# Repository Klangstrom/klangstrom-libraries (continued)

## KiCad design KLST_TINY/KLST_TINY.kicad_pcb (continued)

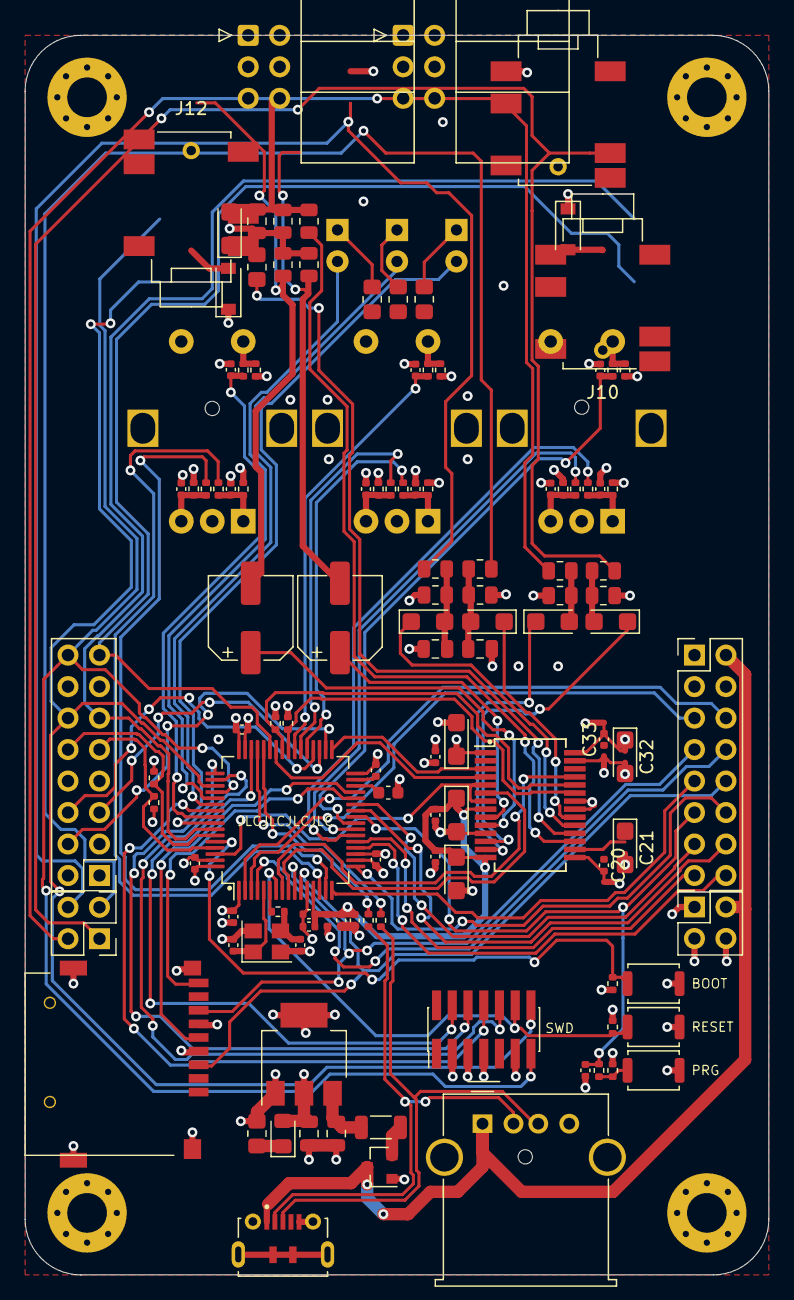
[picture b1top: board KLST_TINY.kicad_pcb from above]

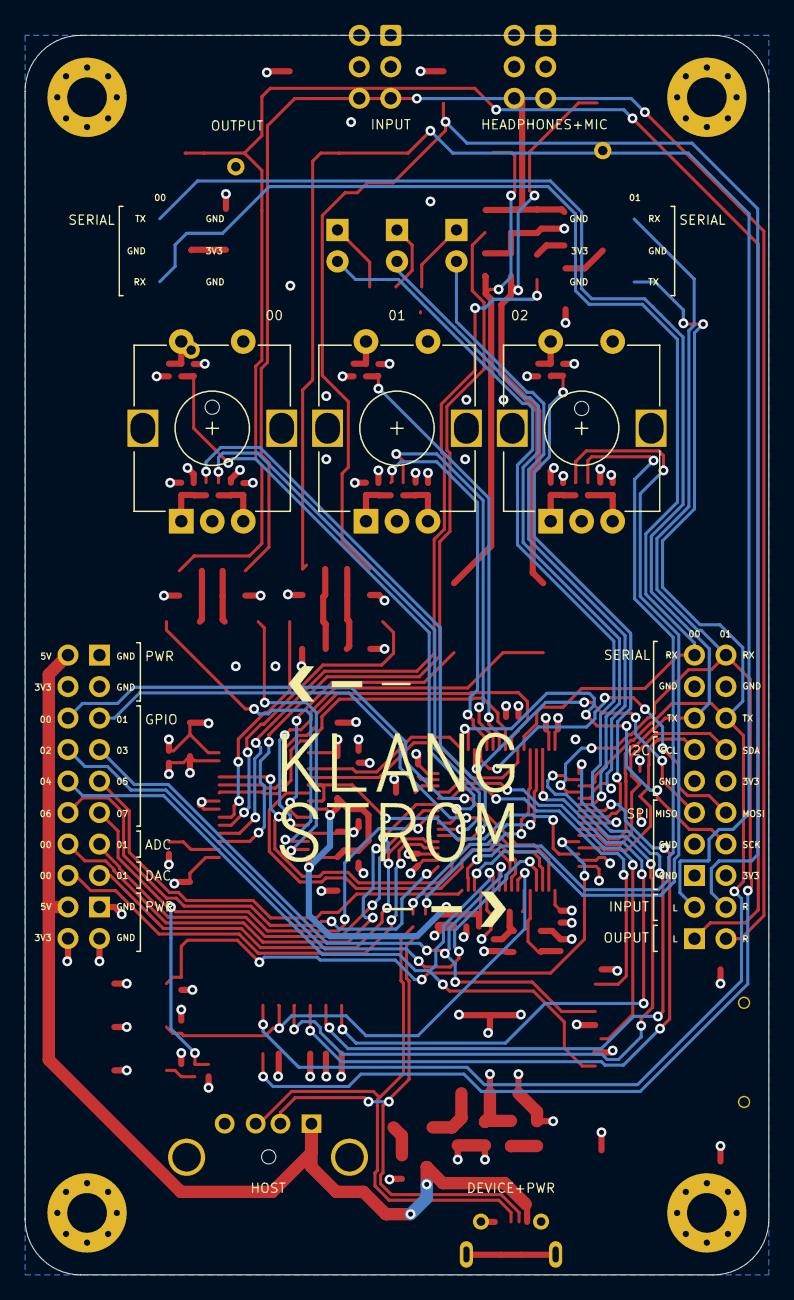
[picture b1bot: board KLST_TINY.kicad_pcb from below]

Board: 4 copper layers, 60.0 x 100.0 mm, 127 parts (7 on the bottom side), 99 nets.

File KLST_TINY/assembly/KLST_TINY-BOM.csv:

Comment,Designator,Footprint,LCSC
"12pF","C1,C2","Capacitor_SMD:C_0402_1005Metric","C1547"
"10nF","C10","Capacitor_SMD:C_0402_1005Metric","C15195"
"220uF","C16,C17","Capacitor_SMD:CP_Elec_6.3x5.4","C3345"
"10uF","C20,C29,C31,C33,C35","Capacitor_Tantalum_SMD:CP_EIA-3216-18_Kemet-A","C7171"
"1uF","C18,C22,C24,C26,C27","Capacitor_Tantalum_SMD:CP_EIA-3216-18_Kemet-A","C7175"
"220pF","C19,C23,C25","Capacitor_SMD:C_0805_2012Metric","C53172"
"10uF","C4,C5","Capacitor_SMD:C_0805_2012Metric","C15850"
"2.2uF","C6","Capacitor_SMD:C_0603_1608Metric","C23630"
"1uF","C7,C9,C11","Capacitor_SMD:C_0402_1005Metric","C52923"
"100nF","C3,C8,C12,C13,C14,C15,C21,C28,C30,C32,C34,C36,C37,C38,C39,C40,C41,C42,C43,C44","Capacitor_SMD:C_0402_1005Metric","C1525"
"LED","D1,D2,D3","LED_THT:LED_D3.0mm","DNF"
"LED","D4","LED_SMD:LED_0805_2012Metric_Pad1.15x1.40mm_HandSolder","C34499"
"D_Schottky","D5,D6","Diode_SMD:D_SOD-123","C8598"
"600Ω@100MHz","FB1","Inductor_SMD:L_1206_3216Metric","C73732"
"MountingHole","H1,H2,H3,H4","MountingHole:MountingHole_3.2mm_M3_Pad_Via","DNF"
"Micro_SD_Card_Card_Detect_SPI","J1","Connector_Card:microSD_SOFNG_TF-015","C113206"
"UART_00","J10","Connector_IDC:IDC-Header_2x03_P2.54mm_Horizontal","C146629"
"ADD-ON_PWR","J11","Connector_PinHeader_2.54mm:PinHeader_2x02_P2.54mm_Vertical","DNF"
"UART_01","J12","Connector_IDC:IDC-Header_2x03_P2.54mm_Horizontal","C146629"
"ADD-ON_AUDIO","J13","Connector_PinHeader_2.54mm:PinHeader_2x02_P2.54mm_Vertical","DNF"
"USB_A","J2","Connector_USB:USB_A_Molex_67643_Horizontal","C293351"
"USB_B_Micro","J3","KLST_TINY:SHOUHAN_MICROXNJ","C404969"
"GPIO+ANALOG_IO_PINS","J4","Connector_PinHeader_2.54mm:PinHeader_2x08_P2.54mm_Vertical","DNF"
"ARM_JTAG_SWD","J5","Connector_PinHeader_1.27mm:PinHeader_2x05_P1.27mm_Vertical_SMD","DNF"
"HEADPHONES+MIC","J6","KLST_TINY:Korean_Hroparts_Elec_PJ-316A-6A","C128987"
"LINE_IN","J7","KLST_TINY:Korean_Hroparts_Elec_PJ-316A-6A","C128987"
"LINE_OUT","J8","KLST_TINY:Korean_Hroparts_Elec_PJ-316A-6A","C128987"
"I2C_00+SPI_00","J9","Connector_PinHeader_2.54mm:PinHeader_2x08_P2.54mm_Vertical","DNF"
"39nH","L1","Inductor_SMD:L_0402_1005Metric","C26443"
"AO3401A","Q1","Package_TO_SOT_SMD:SOT-23","C693260"
"47K","R10,R11,R16,R22,R24","Resistor_SMD:R_0805_2012Metric","C17713"
"680R","R12","Resistor_SMD:R_0805_2012Metric","C17798"
"2.2K","R13,R14,R43,R44","Resistor_SMD:R_0402_1005Metric","C25879"
"330R","R15","Resistor_SMD:R_0805_2012Metric_Pad1.20x1.40mm_HandSolder","C17630"
"5.6K","R17,R18,R19,R20","Resistor_SMD:R_0805_2012Metric","C4382"
"22R","R1,R2","Resistor_SMD:R_0402_1005Metric","C25092"
"100R","R21,R23","Resistor_SMD:R_0805_2012Metric","C17408"
"1K","R26,R32,R38,R46","Resistor_SMD:R_0402_1005Metric","C11702"
"10R","R3","Resistor_SMD:R_0402_1005Metric","C25077"
"1K","R4,R5,R6,R7","Resistor_SMD:R_0805_2012Metric_Pad1.20x1.40mm_HandSolder","C17513"
"10K","R8,R9,R25,R27,R28,R29,R30,R31,R33,R34,R35,R36,R37,R39,R40,R41,R42,R45","Resistor_SMD:R_0402_1005Metric","C25744"
"BUTTON_BOOT_FLASH","SW1","Button_Switch_SMD:SW_Push_SPST_NO_Alps_SKRK","C115357"
"BUTTON_RESET","SW2","Button_Switch_SMD:SW_Push_SPST_NO_Alps_SKRK","C115357"
"ENCODER","SW3,SW4,SW5","Rotary_Encoder:RotaryEncoder_Alps_EC12E-Switch_Vertical_H20mm","DNF"
"BUTTON","SW6","Button_Switch_SMD:SW_Push_SPST_NO_Alps_SKRK","C115357"
"STM32F446RETx","U1","Package_QFP:LQFP-64_10x10mm_P0.5mm","C69336"
"AMS1117-3.3","U2","Package_TO_SOT_SMD:SOT-223-3_TabPin2","C6186"
"WM8731SEDS","U3","Package_SO:SSOP-28_5.3x10.2mm_P0.65mm","C323837"
"16MHz","Y1","Crystal:Crystal_SMD_3225-4Pin_3.2x2.5mm","C13738"

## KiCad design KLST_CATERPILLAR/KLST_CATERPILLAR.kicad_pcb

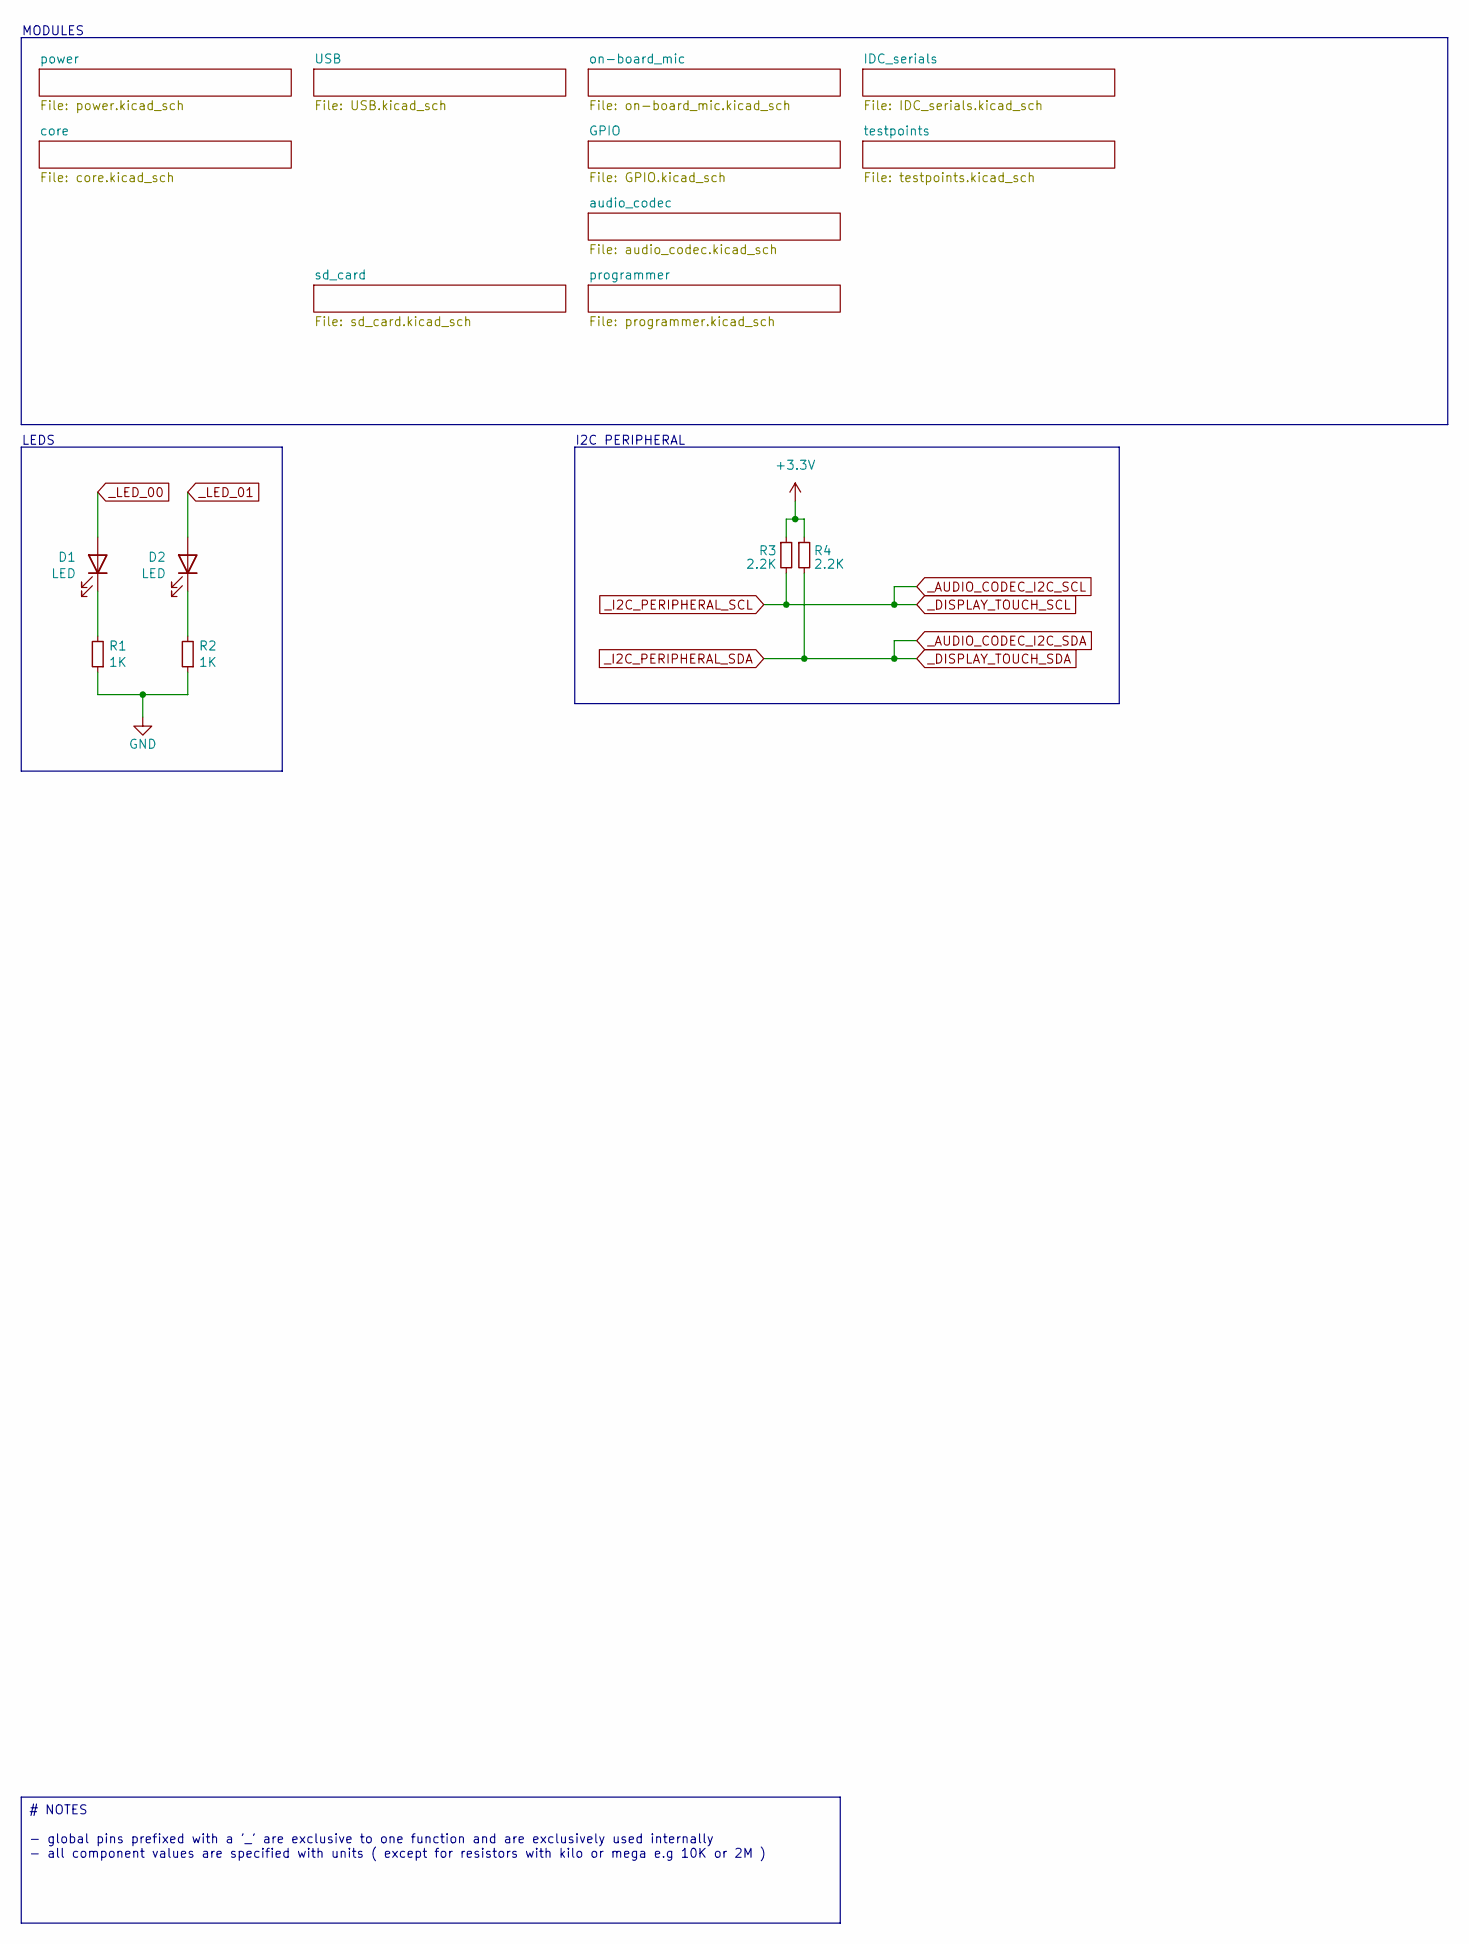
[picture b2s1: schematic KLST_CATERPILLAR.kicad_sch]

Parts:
D1, D2: LED; LED_0805_2012Metric; JLCPCB C34499
R1, R2: 1K; R_0805_2012Metric_Pad1.20x1.40mm_HandSolder; JLCPCB C17513
R3, R4: 2.2K; R_0402_1005Metric; JLCPCB C966835

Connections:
unnamed: D1.1 (K), R1.2
unnamed: D2.1 (K), R2.2
_AUDIO_CODEC_I2C_SCL: R3.2; also elsewhere on the board
_AUDIO_CODEC_I2C_SDA: R4.2; also elsewhere on the board
_LED_00: D1.2 (A); also elsewhere on the board
_LED_01: D2.2 (A); also elsewhere on the board

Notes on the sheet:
# NOTES - global pins prefixed with a '_' are exclusive to one function and are exclusively used internally - all component values are specified with units ( except for resistors with kilo or mega e.g 10K or 2M )
LEDS
I2C PERIPHERAL
MODULES

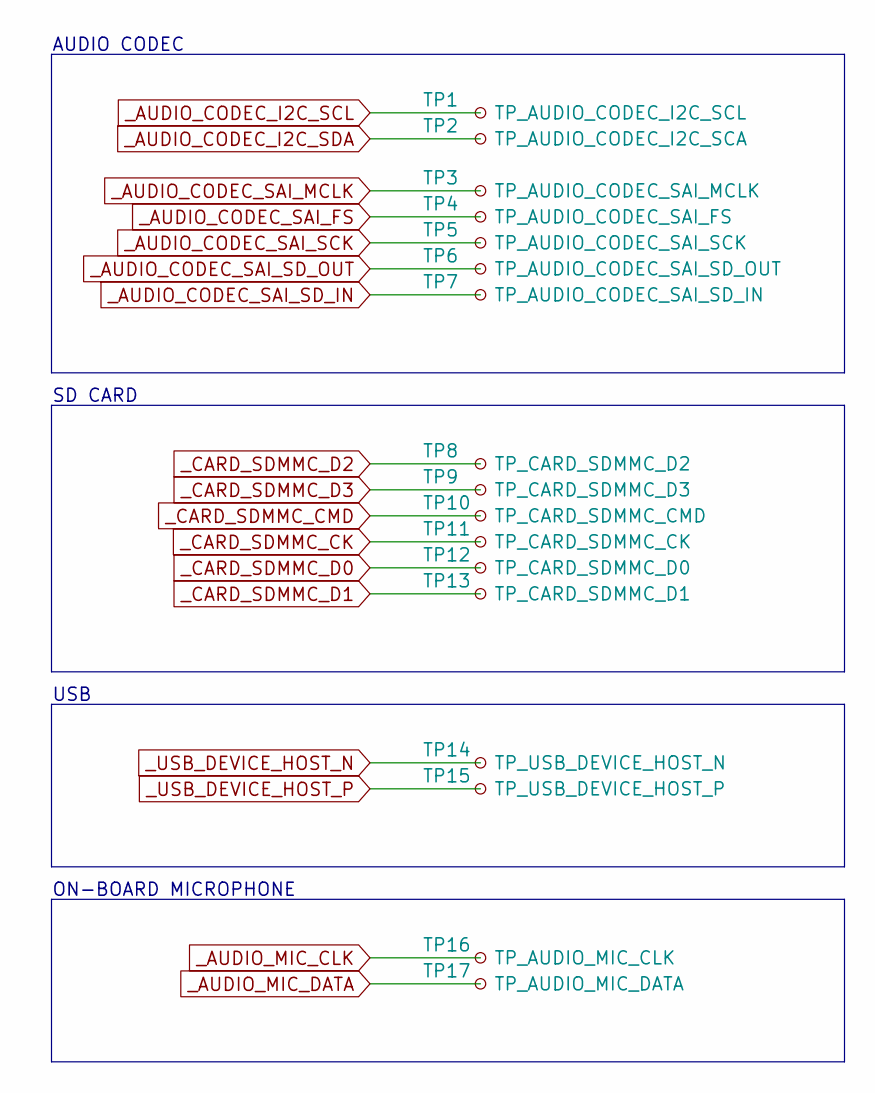
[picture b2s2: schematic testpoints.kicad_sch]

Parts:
TP1: TP_AUDIO_CODEC_I2C_SCL; TestPoint_Pad_D1.5mm
TP2: TP_AUDIO_CODEC_I2C_SCA; TestPoint_Pad_D1.5mm
TP3: TP_AUDIO_CODEC_SAI_MCLK; TestPoint_Pad_D1.5mm
TP4: TP_AUDIO_CODEC_SAI_FS; TestPoint_Pad_D1.5mm
TP5: TP_AUDIO_CODEC_SAI_SCK; TestPoint_Pad_D1.5mm
TP6: TP_AUDIO_CODEC_SAI_SD_OUT; TestPoint_Pad_D1.5mm
TP7: TP_AUDIO_CODEC_SAI_SD_IN; TestPoint_Pad_D1.5mm
TP8: TP_CARD_SDMMC_D2; TestPoint_Pad_D1.5mm
TP9: TP_CARD_SDMMC_D3; TestPoint_Pad_D1.5mm
TP10: TP_CARD_SDMMC_CMD; TestPoint_Pad_D1.5mm
TP11: TP_CARD_SDMMC_CK; TestPoint_Pad_D1.5mm
TP12: TP_CARD_SDMMC_D0; TestPoint_Pad_D1.5mm
TP13: TP_CARD_SDMMC_D1; TestPoint_Pad_D1.5mm
TP14: TP_USB_DEVICE_HOST_N; TestPoint_Pad_D1.5mm
TP15: TP_USB_DEVICE_HOST_P; TestPoint_Pad_D1.5mm
TP16: TP_AUDIO_MIC_CLK; TestPoint_Pad_D1.5mm
TP17: TP_AUDIO_MIC_DATA; TestPoint_Pad_D1.5mm

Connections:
_AUDIO_CODEC_I2C_SCL: TP1.1; also elsewhere on the board
_AUDIO_CODEC_I2C_SDA: TP2.1; also elsewhere on the board
_AUDIO_CODEC_SAI_FS: TP4.1; also elsewhere on the board
_AUDIO_CODEC_SAI_MCLK: TP3.1; also elsewhere on the board
_AUDIO_CODEC_SAI_SCK: TP5.1; also elsewhere on the board
_AUDIO_CODEC_SAI_SD_IN: TP7.1; also elsewhere on the board
_AUDIO_CODEC_SAI_SD_OUT: TP6.1; also elsewhere on the board
_AUDIO_MIC_CLK: TP16.1; also elsewhere on the board
_AUDIO_MIC_DATA: TP17.1; also elsewhere on the board
_CARD_SDMMC_CK: TP11.1; also elsewhere on the board
_CARD_SDMMC_CMD: TP10.1; also elsewhere on the board
_CARD_SDMMC_D0: TP12.1; also elsewhere on the board
_CARD_SDMMC_D1: TP13.1; also elsewhere on the board
_CARD_SDMMC_D2: TP8.1; also elsewhere on the board
_CARD_SDMMC_D3: TP9.1; also elsewhere on the board
_USB_DEVICE_HOST_N: TP14.1; also elsewhere on the board
_USB_DEVICE_HOST_P: TP15.1; also elsewhere on the board

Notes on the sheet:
USB
SD CARD
ON-BOARD MICROPHONE
AUDIO CODEC

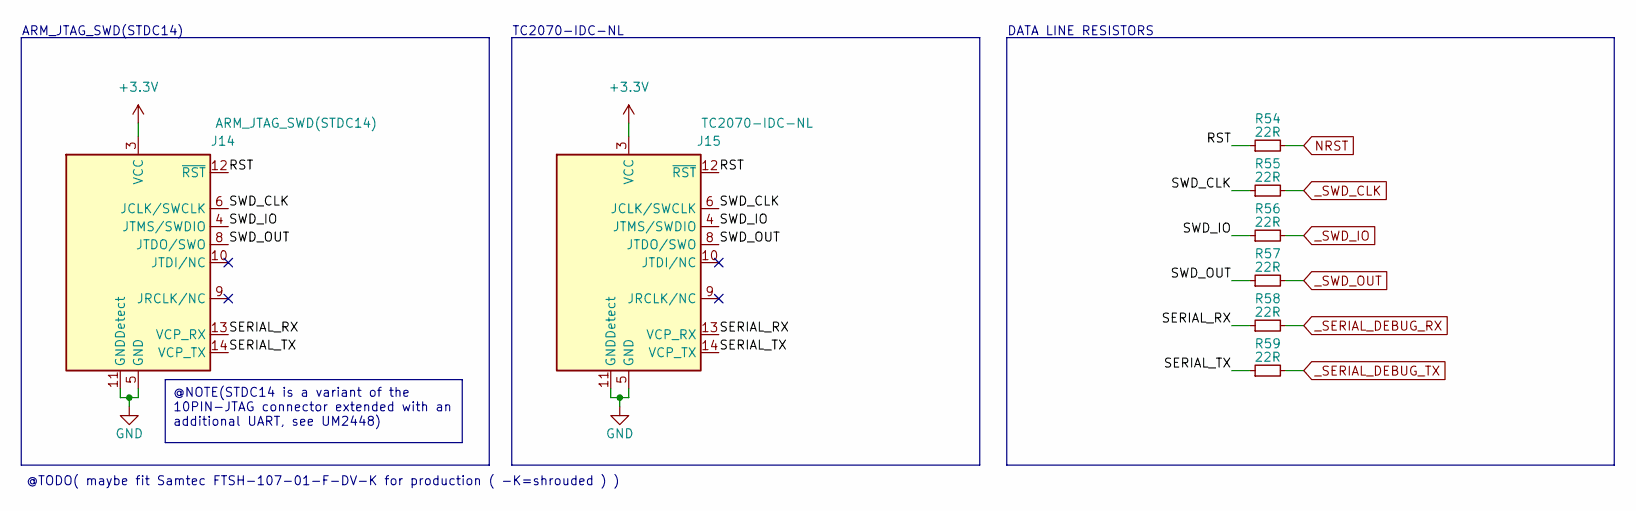
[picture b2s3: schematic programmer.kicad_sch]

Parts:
J14: ARM_JTAG_SWD(STDC14); PinHeader_2x07_P1.27mm_Vertical_SMD; JLCPCB C2881912
J15: TC2070-IDC-NL; JLCPCB DNF
R54, R55, R56, R57, R58, R59: 22R; R_0402_1005Metric; JLCPCB C114765

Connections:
/programmer/RST: J14.12 (~RST), J15.12 (~RST), R54.1
/programmer/SERIAL_RX: J14.13 (VCP_RX), J15.13 (VCP_RX), R58.1
/programmer/SERIAL_TX: J14.14 (VCP_TX), J15.14 (VCP_TX), R59.1
/programmer/SWD_IO: J14.4 (JTMS/SWDIO), J15.4 (JTMS/SWDIO), R56.1
/programmer/SWD_OUT: J14.8 (JTDO/SWO), J15.8 (JTDO/SWO), R57.1
NRST: R54.2; also elsewhere on the board
_SERIAL_DEBUG_RX: R58.2; also elsewhere on the board
_SERIAL_DEBUG_TX: R59.2; also elsewhere on the board
_SWD_IO: R56.2; also elsewhere on the board
_SWD_OUT: R57.2; also elsewhere on the board

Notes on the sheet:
@NOTE(STDC14 is a variant of the 10PIN-JTAG connector extended with an additional UART, see UM2448)
DATA LINE RESISTORS
@TODO( maybe fit Samtec FTSH-107-01-F-DV-K for production ( -K=shrouded ) )
ARM_JTAG_SWD(STDC14)
TC2070-IDC-NL

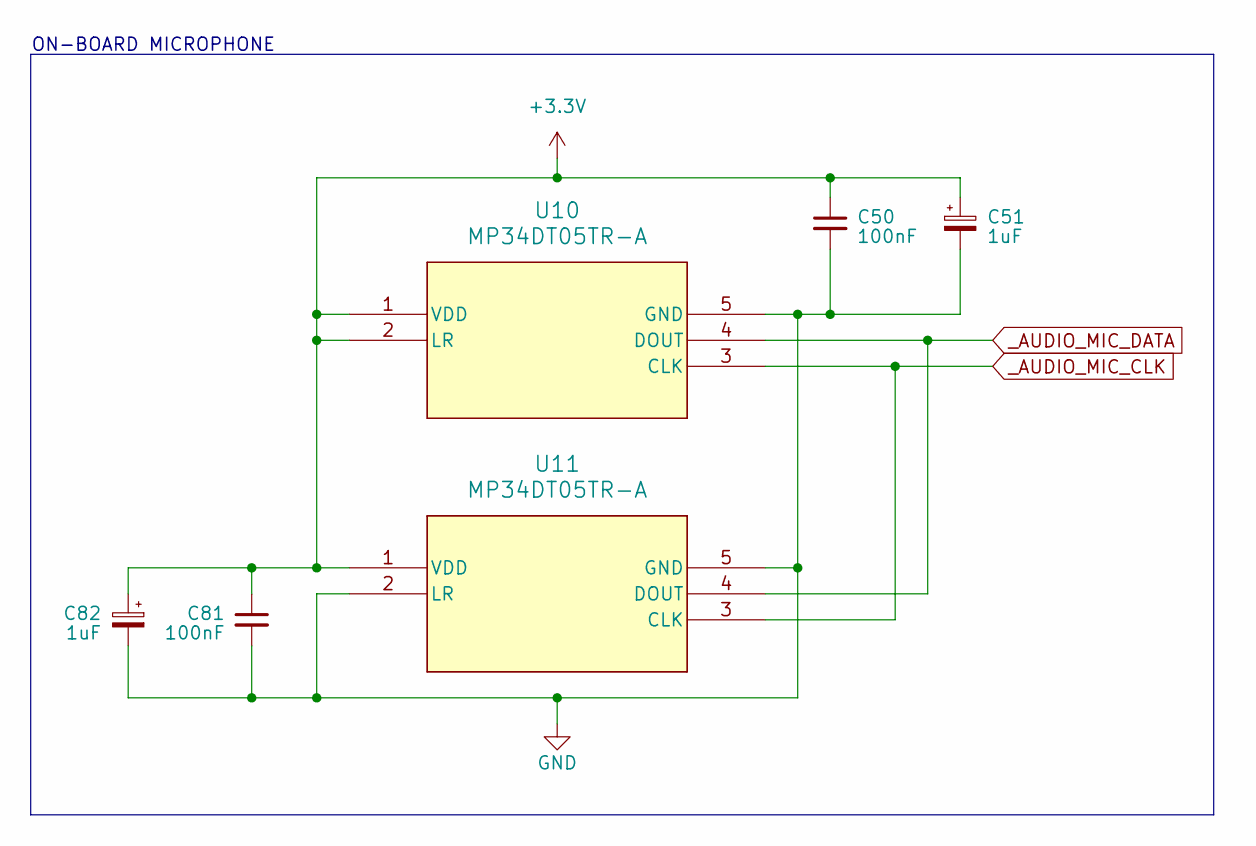
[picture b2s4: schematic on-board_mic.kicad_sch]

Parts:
C50, C81: 100nF; C_0402_1005Metric; JLCPCB C1525
C51, C82: 1uF; C_0402_1005Metric; JLCPCB C52923
U10, U11: MP34DT05TR-A; MP34DT05TR-A_STM; JLCPCB C2688664

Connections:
_AUDIO_MIC_CLK: U10.3 (CLK), U11.3 (CLK); also elsewhere on the board
_AUDIO_MIC_DATA: U10.4 (DOUT), U11.4 (DOUT); also elsewhere on the board

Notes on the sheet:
ON-BOARD MICROPHONE

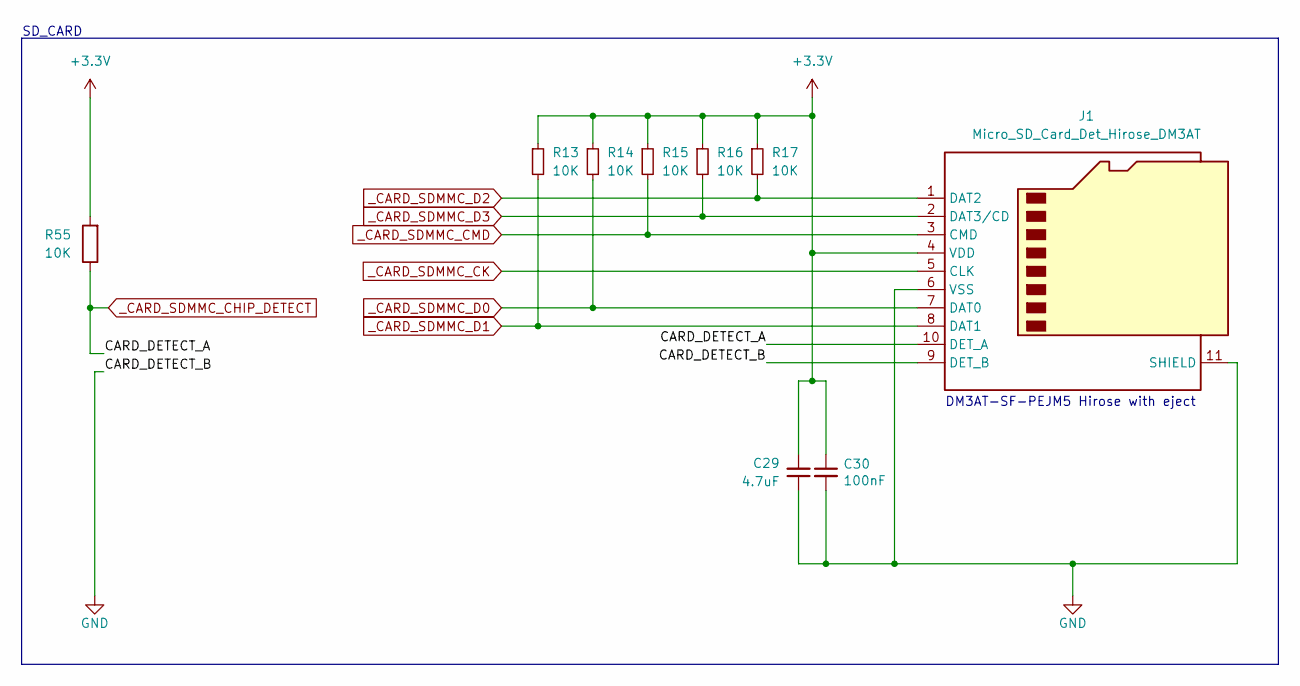
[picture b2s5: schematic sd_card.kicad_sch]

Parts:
C29: 4.7uF; C_0402_1005Metric; JLCPCB C23733
C30: 100nF; C_0402_1005Metric; JLCPCB C1525
J1: Micro_SD_Card_Det_Hirose_DM3AT; microSD_HC_Hirose_DM3AT-SF-PEJM5; JLCPCB C114218
R13, R14, R15, R16, R17, R55: 10K; R_0402_1005Metric; JLCPCB C25744

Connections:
_CARD_SDMMC_CK: J1.5 (CLK); also elsewhere on the board
_CARD_SDMMC_CMD: J1.3 (CMD), R15.2; also elsewhere on the board
_CARD_SDMMC_D0: J1.7 (DAT0), R14.2; also elsewhere on the board
_CARD_SDMMC_D1: J1.8 (DAT1), R13.2; also elsewhere on the board
_CARD_SDMMC_D2: J1.1 (DAT2), R17.2; also elsewhere on the board
_CARD_SDMMC_D3: J1.2 (DAT3/CD), R16.2; also elsewhere on the board

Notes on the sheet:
SD_CARD
DM3AT-SF-PEJM5 Hirose with eject

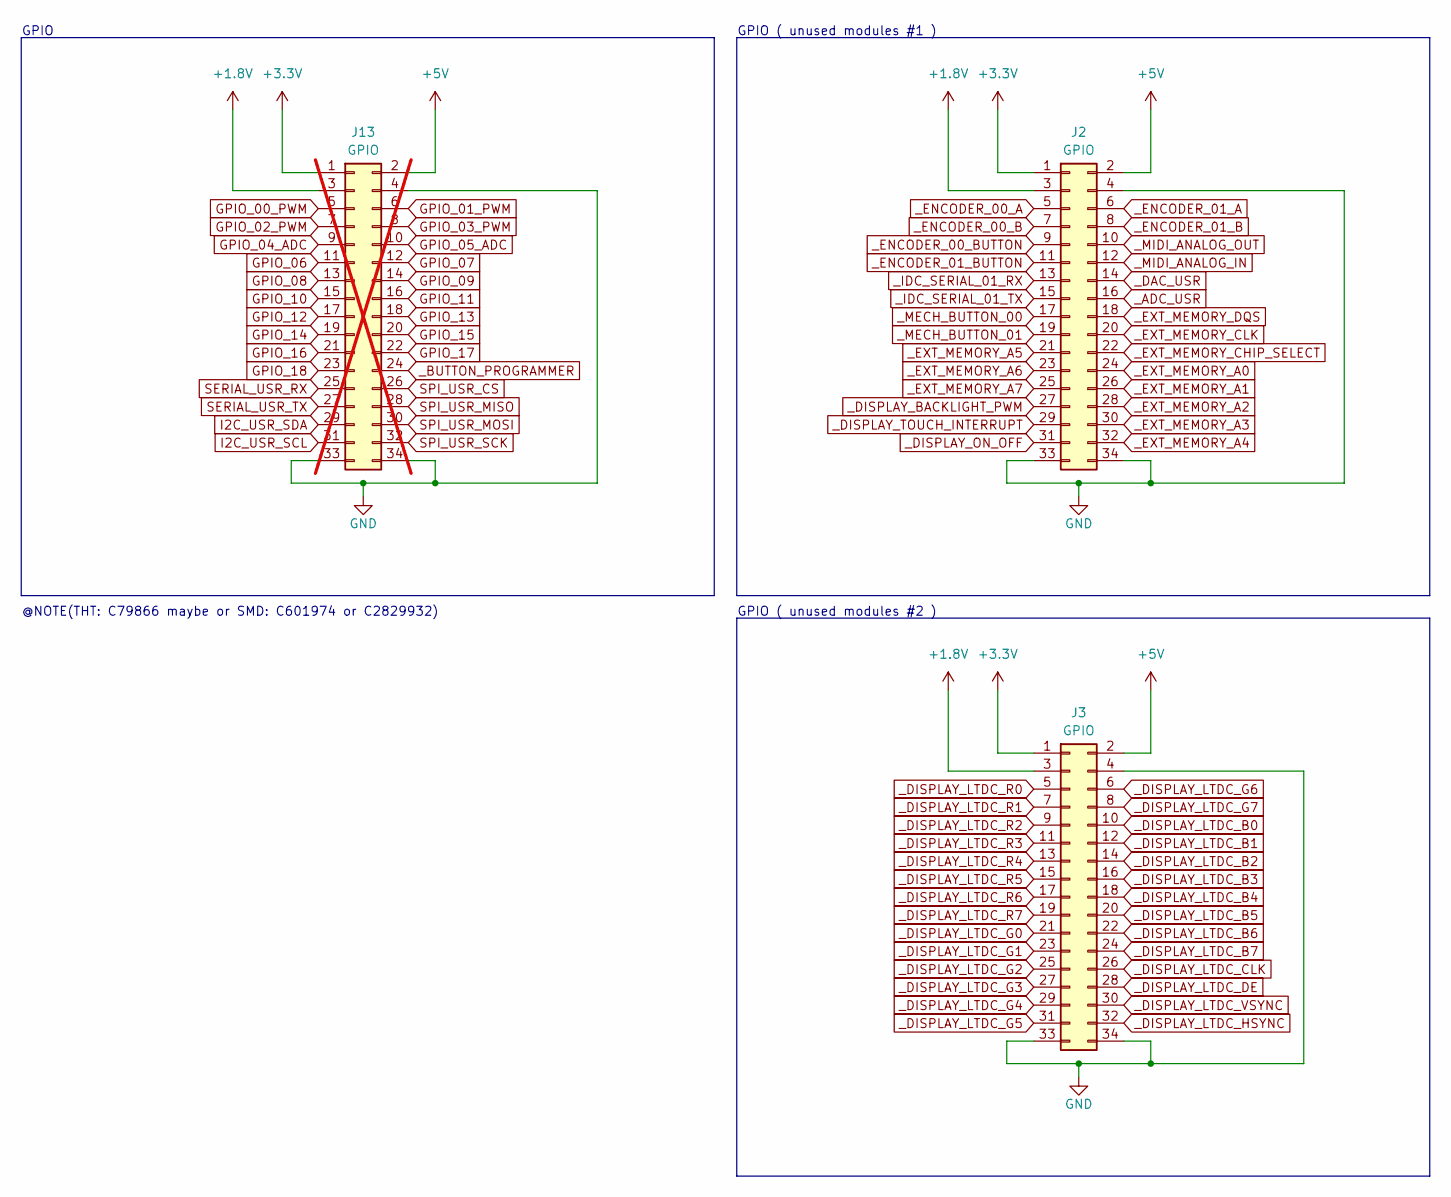
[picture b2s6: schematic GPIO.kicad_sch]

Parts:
J2, J3: GPIO; IDC-Header_2x17_P2.54mm_Horizontal; JLCPCB C79866
J13: GPIO; IDC-PinHeader_2x17_P2.54mm_Vertical_SMD; JLCPCB C2829932; not fitted

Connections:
+5V: J2.2, J3.2, J13.2; also elsewhere on the board
GPIO_00_PWM: J13.5; also elsewhere on the board
GPIO_02_PWM: J13.7; also elsewhere on the board
GPIO_03_PWM: J13.8; also elsewhere on the board
GPIO_04_ADC: J13.9; also elsewhere on the board
GPIO_05_ADC: J13.10; also elsewhere on the board
GPIO_06: J13.11; also elsewhere on the board
GPIO_07: J13.12; also elsewhere on the board
GPIO_08: J13.13; also elsewhere on the board
GPIO_09: J13.14; also elsewhere on the board
GPIO_10: J13.15; also elsewhere on the board
GPIO_11: J13.16; also elsewhere on the board
GPIO_12: J13.17; also elsewhere on the board
GPIO_13: J13.18; also elsewhere on the board
GPIO_14: J13.19; also elsewhere on the board
GPIO_15: J13.20; also elsewhere on the board
GPIO_16: J13.21; also elsewhere on the board
GPIO_17: J13.22; also elsewhere on the board
GPIO_18: J13.23; also elsewhere on the board
I2C_USR_SCL: J13.31; also elsewhere on the board
I2C_USR_SDA: J13.29; also elsewhere on the board
SERIAL_USR_RX: J13.25; also elsewhere on the board
SERIAL_USR_TX: J13.27; also elsewhere on the board
SPI_USR_CS: J13.26; also elsewhere on the board
SPI_USR_MISO: J13.28; also elsewhere on the board
SPI_USR_MOSI: J13.30; also elsewhere on the board
SPI_USR_SCK: J13.32; also elsewhere on the board
_BUTTON_PROGRAMMER: J13.24; also elsewhere on the board

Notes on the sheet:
@NOTE(THT: C79866 maybe or SMD: C601974 or C2829932)
GPIO ( unused modules #2 )
GPIO ( unused modules #1 )
GPIO

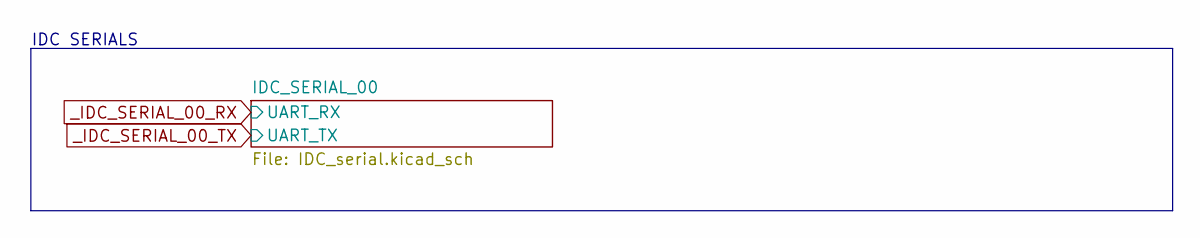
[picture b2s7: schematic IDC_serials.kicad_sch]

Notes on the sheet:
IDC SERIALS

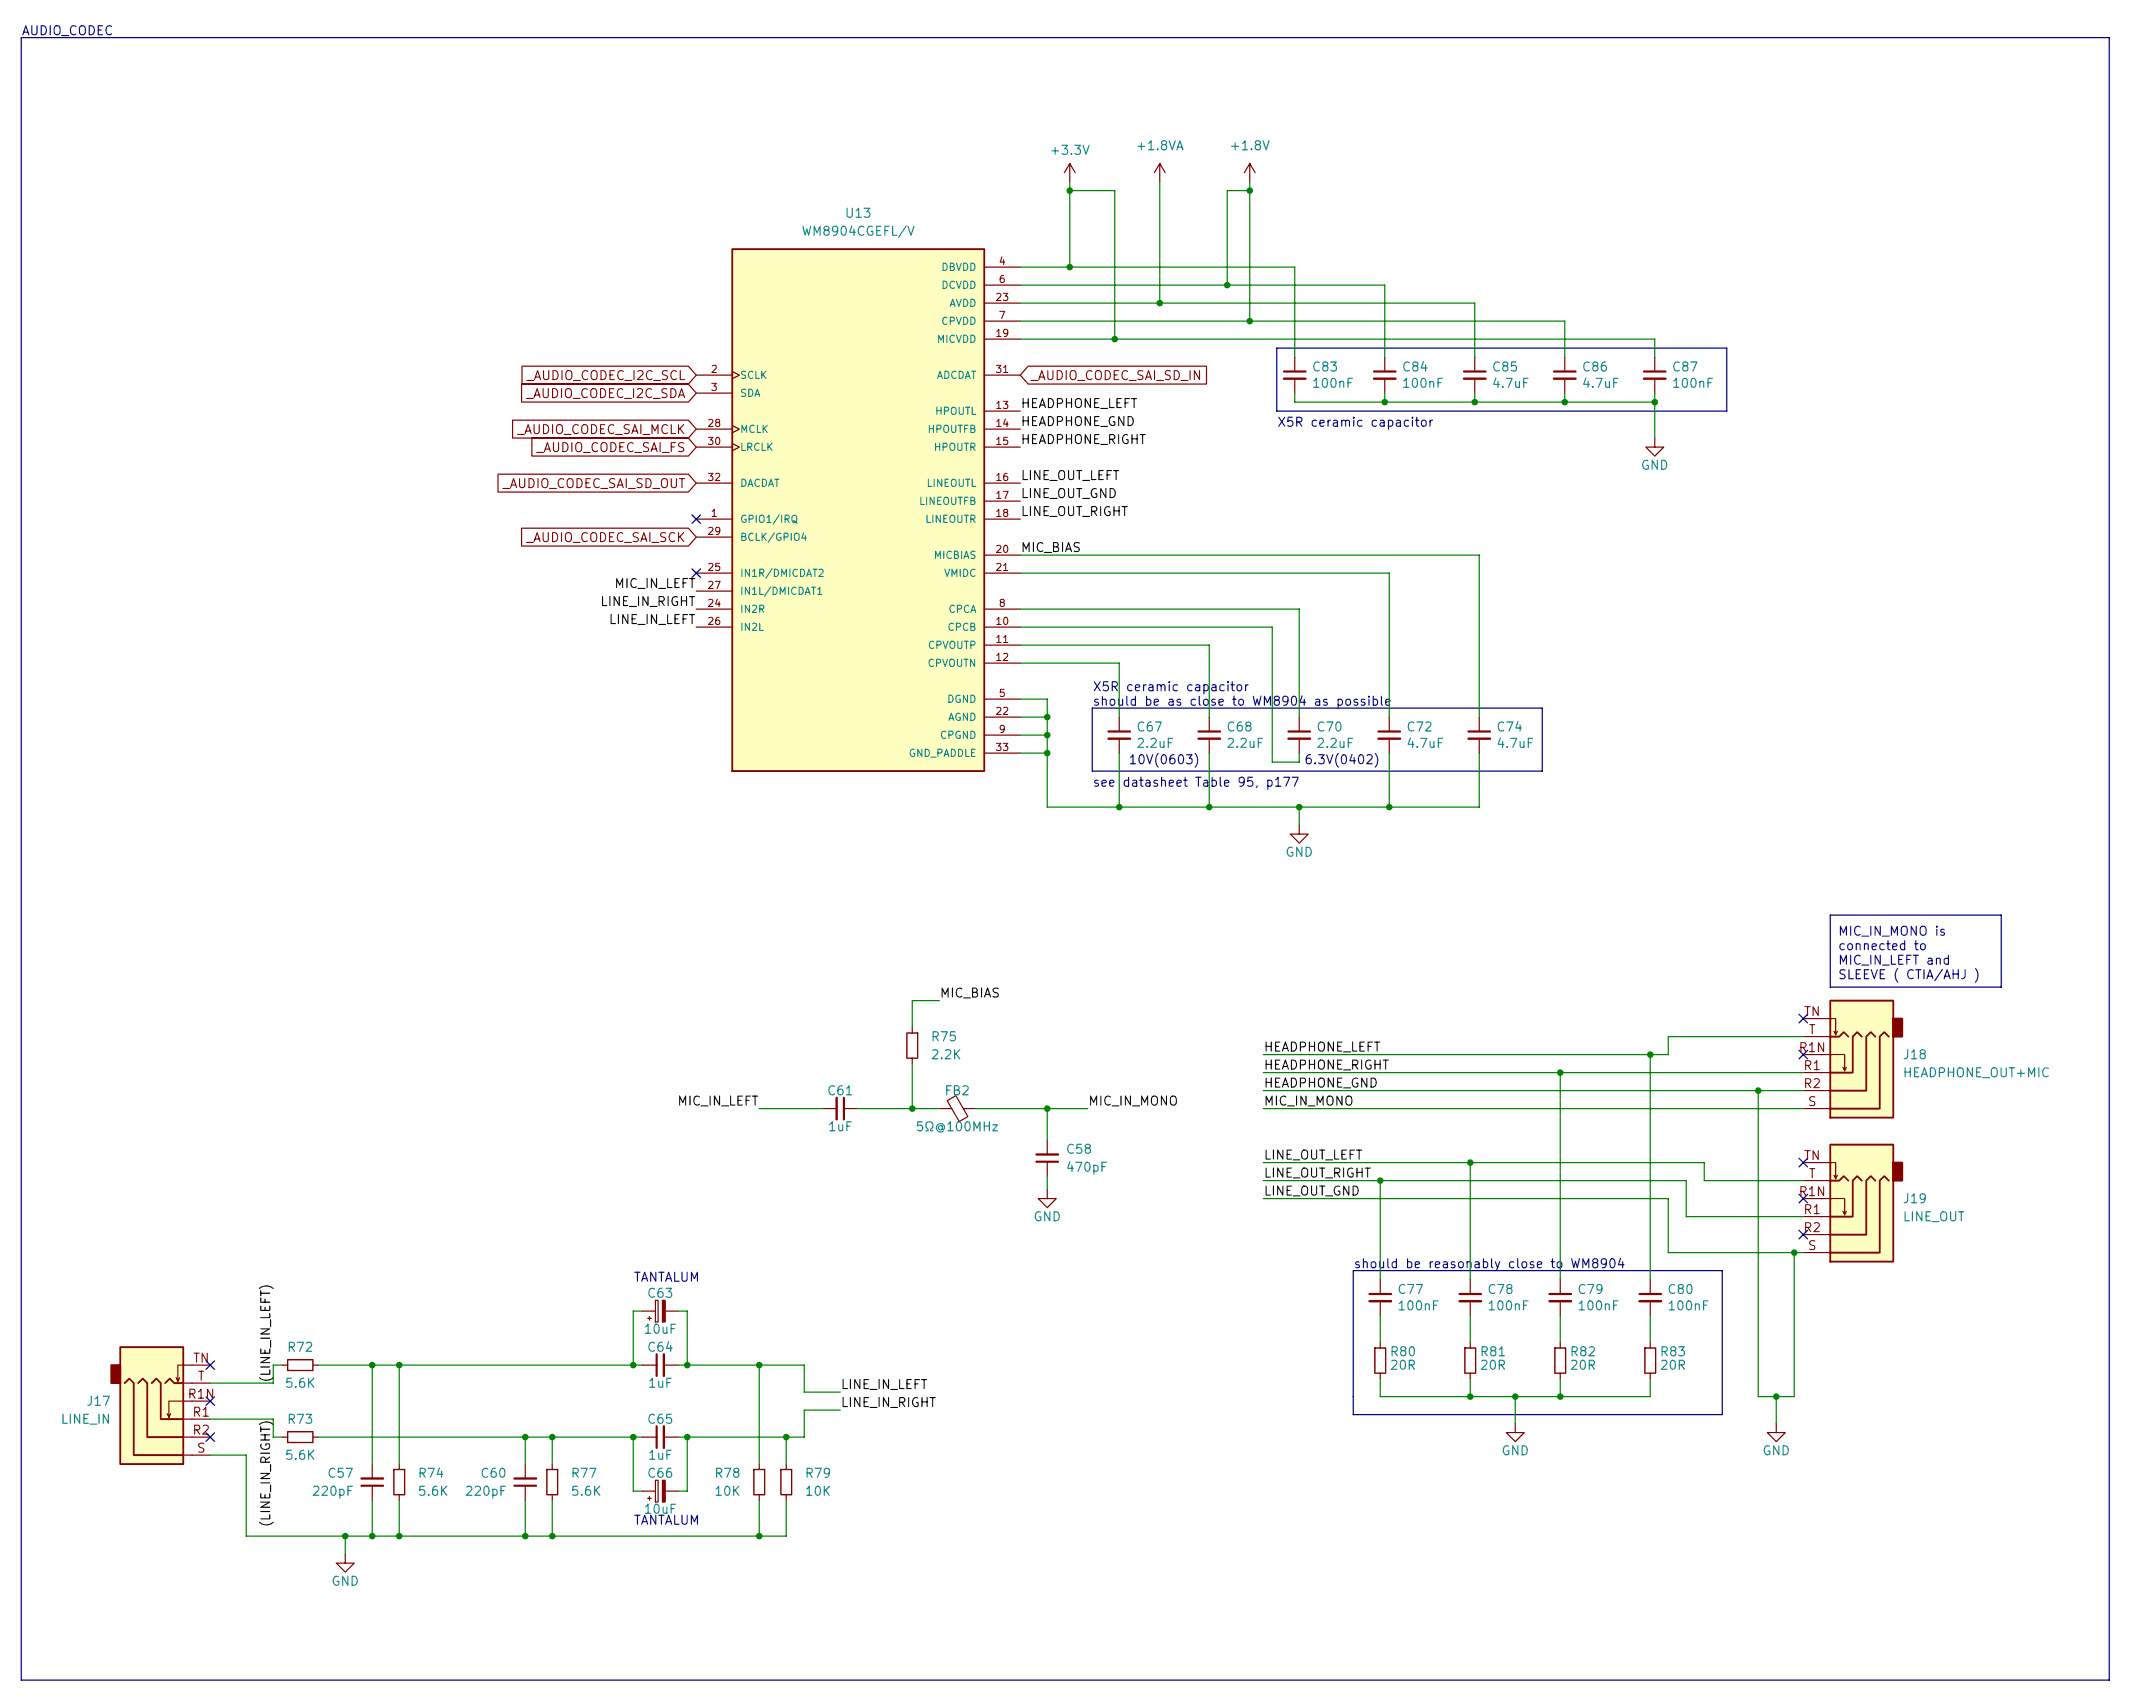
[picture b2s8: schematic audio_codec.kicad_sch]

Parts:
C57, C60: 220pF; C_0402_1005Metric; JLCPCB C1530
C58: 470pF; C_0402_1005Metric; JLCPCB C1537
C61, C64, C65: 1uF; C_0402_1005Metric; JLCPCB C52923
C63, C66: 10uF; CP_EIA-3216-18_Kemet-A; JLCPCB C7171
C67, C68: 2.2uF; C_0603_1608Metric; JLCPCB C86013
C70: 2.2uF; C_0402_1005Metric; JLCPCB C452745
C72, C74, C85, C86: 4.7uF; C_0402_1005Metric; JLCPCB C23733
C77, C78, C79, C80, C83, C84, C87: 100nF; C_0402_1005Metric; JLCPCB C1525
FB2: 5Ω@100MHz; L_0402_1005Metric; JLCPCB C160969
J17: LINE_IN; PJ-316A-6A; JLCPCB C128987
J18: HEADPHONE_OUT+MIC; PJ-316A-6A; JLCPCB C128987
J19: LINE_OUT; PJ-316A-6A; JLCPCB C128987
R72, R73, R74, R77: 5.6K; R_0603_1608Metric; JLCPCB C417107
R75: 2.2K; R_0402_1005Metric; JLCPCB C966835
R78, R79: 10K; R_0603_1608Metric; JLCPCB C2924143
R80, R81, R82, R83: 20R; R_0603_1608Metric; JLCPCB C544033
U13: WM8904CGEFL/V; QFN40P400X400X80-33N; JLCPCB C323845

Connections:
+1.8VA: C85.1, U13.23 (AVDD); also elsewhere on the board
/audio_codec/(LINE_IN_LEFT): J17.T, R72.1
/audio_codec/(LINE_IN_RIGHT): J17.R1, R73.1
/audio_codec/HEADPHONE_LEFT: C80.1, J18.T, U13.13 (HPOUTL)
/audio_codec/HEADPHONE_RIGHT: C79.1, J18.R1, U13.15 (HPOUTR)
/audio_codec/LINE_IN_LEFT: C63.2, C64.2, R78.1, U13.26 (IN2L)
/audio_codec/LINE_IN_RIGHT: C65.2, C66.2, R79.1, U13.24 (IN2R)
/audio_codec/LINE_OUT_LEFT: C78.1, J19.T, U13.16 (LINEOUTL)
/audio_codec/LINE_OUT_RIGHT: C77.1, J19.R1, U13.18 (LINEOUTR)
/audio_codec/MIC_BIAS: C74.1, R75.1, U13.20 (MICBIAS)
/audio_codec/MIC_IN_LEFT: C61.2, U13.27 (IN1L/DMICDAT1)
/audio_codec/MIC_IN_MONO: C58.2, FB2.1, J18.S
unnamed: C57.2, C63.1, C64.1, R72.2, R74.1
unnamed: C60.2, C65.1, C66.1, R73.2, R77.1
unnamed: C61.1, FB2.2, R75.2
unnamed: C77.2, R80.1
unnamed: C78.2, R81.1
unnamed: C79.2, R82.1
unnamed: C80.2, R83.1
unnamed: C70.1, U13.8 (CPCA)
unnamed: C70.2, U13.10 (CPCB)
unnamed: C67.1, U13.12 (CPVOUTN)
unnamed: C68.1, U13.11 (CPVOUTP)
unnamed: C72.1, U13.21 (VMIDC)
_AUDIO_CODEC_I2C_SCL: U13.2 (SCLK); also elsewhere on the board
_AUDIO_CODEC_I2C_SDA: U13.3 (SDA); also elsewhere on the board
_AUDIO_CODEC_SAI_FS: U13.30 (LRCLK); also elsewhere on the board
_AUDIO_CODEC_SAI_MCLK: U13.28 (MCLK); also elsewhere on the board
_AUDIO_CODEC_SAI_SCK: U13.29 (BCLK/GPIO4); also elsewhere on the board
_AUDIO_CODEC_SAI_SD_IN: U13.31 (ADCDAT); also elsewhere on the board
_AUDIO_CODEC_SAI_SD_OUT: U13.32 (DACDAT); also elsewhere on the board

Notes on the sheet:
MIC_IN_MONO is connected to MIC_IN_LEFT and SLEEVE ( CTIA/AHJ )
see datasheet Table 95, p177
X5R ceramic capacitor should be as close to WM8904 as possible
AUDIO_CODEC
TANTALUM
10V(0603)
should be reasonably close to WM8904
X5R ceramic capacitor
6.3V(0402)

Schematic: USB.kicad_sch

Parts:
C46: 1uF; C_0805_2012Metric; JLCPCB C307362
C47, C48: 100nF; C_1206_3216Metric; JLCPCB C3015151
C49: 47uF; CP_Elec_4x5.4; JLCPCB C114447
D12, D13: SP0503BAHT; SOT-143; JLCPCB C3040626
J9: DEVICE+CHARGE(UFP); USB_C_Receptacle_HRO_TYPE-C-31-M-12; JLCPCB C165948
J10: HOST(DFP); USB_C_Receptacle_HRO_TYPE-C-31-M-12; JLCPCB C165948
R43, R44: 5.1K; R_0402_1005Metric; JLCPCB C409730
R45, R46: 56K; R_0402_1005Metric; JLCPCB C352409
U7: ECMF02-2AMX6; ST_UQFN-6L_1.5x1.7mm_P0.5mm; JLCPCB C2651144
U8: TPS2041B; SOT-23-5; JLCPCB C51386

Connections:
+5V: C47.1, D13.4 (K), R45.2, R46.2, U8.5 (IN); also elsewhere on the board
/USB/USB_CONNECTOR_MINUS: D12.3 (K), D13.3 (K), J9.A7 (D-), J9.B7 (D-), J10.A7 (D-), J10.B7 (D-), U7.2 (D-_in)
/USB/USB_CONNECTOR_PLUS: D12.2 (K), D13.2 (K), J9.A6 (D+), J9.B6 (D+), J10.A6 (D+), J10.B6 (D+), U7.1 (D+_in)
/USB/VBUS_HOST_OUT: C48.1, C49.1, J10.A4 (VBUS), J10.A9 (VBUS), J10.B4 (VBUS), J10.B9 (VBUS), U8.1 (OUT)
unnamed: J9.A5 (CC1), R43.2
unnamed: J9.B5 (CC2), R44.2
unnamed: J10.A5 (CC1), R45.1
unnamed: J10.B5 (CC2), R46.1
_USB_DEVICE_HOST_N: U7.5 (D-_out); also elsewhere on the board
_USB_DEVICE_HOST_P: U7.6 (D+_out); also elsewhere on the board
_USB_DEVICE_HOST_VBUS: C46.1, D12.4 (K), J9.A4 (VBUS), J9.A9 (VBUS), J9.B4 (VBUS), J9.B9 (VBUS); also elsewhere on the board

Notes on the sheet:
Rd: pull-down resistor ( fixed at 5.1K )
Rp: pull-up resisitor ( 56K to VBUS(5V) for default USB power )
FILTER + ESD PROTECTION
see typical application datasheet, p20
HOST
TPS2041B rated at 500mA
DEVICE+CHARGE
POWER-DISTRIBUTION SWITCHES
